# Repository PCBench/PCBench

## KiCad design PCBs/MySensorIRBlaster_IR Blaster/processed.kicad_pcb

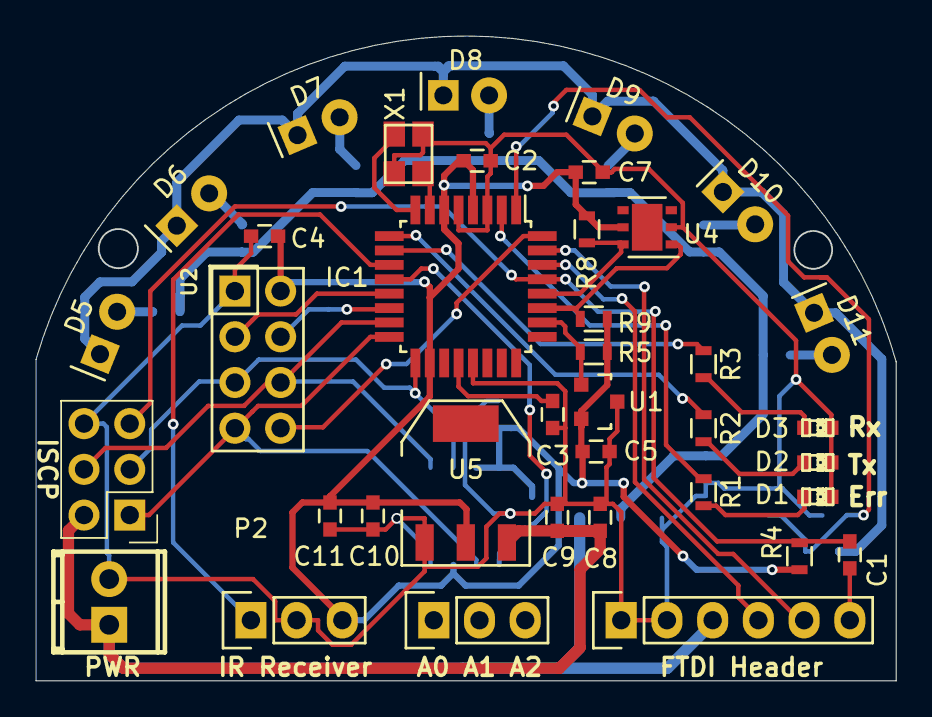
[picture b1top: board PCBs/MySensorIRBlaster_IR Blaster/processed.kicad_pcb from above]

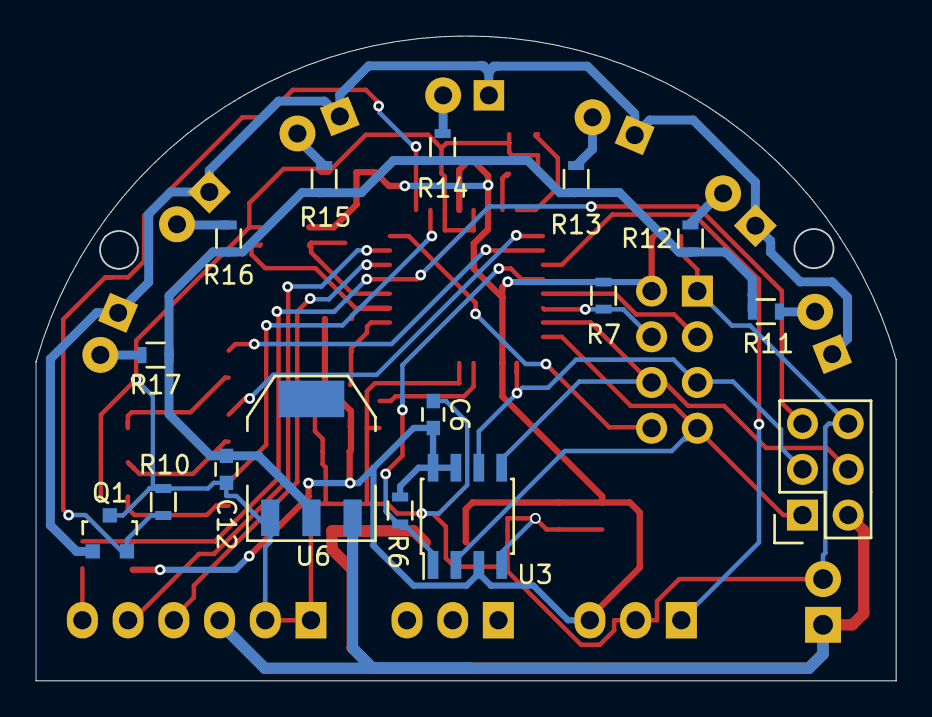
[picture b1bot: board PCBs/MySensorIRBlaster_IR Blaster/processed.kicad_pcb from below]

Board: 2 copper layers, 47.8 x 35.8 mm, 53 parts (16 on the bottom side), 37 nets.

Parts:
C1, C2, C3, C4, C5, C6, C7, C9, C11: 0.1uF; C_0603
C8, C10: 10uF; C_0603
C12: 22uF; C_0603
CON1: AVR-ISP-6; Socket_Strip_Straight_2x03
D1: Err; LED-0603
D2: Tx; LED-0603
D3: Rx; LED-0603
D5, D6, D7, D8, D9, D10, D11: IR LED; LED-5MM-Horizontal
IC1: ATMEGA328P-A; TQFP-32_7x7mm_Pitch0.8mm
P1: FTDI Header; Pin_Header_Straight_1x06
P2: IR Receiver; Socket_Strip_Straight_1x03
P3: Analog IN; Pin_Header_Straight_1x03
P4: PWR; TerminalBlock2.54mmx2-kcswalter
Q1: FDV303N; SOT-23
R1, R2, R3, R11, R12, R13, R14, R15, R16, R17: R; R_0603
R4: 10K; R_0603
R5, R6, R7, R8, R9, R10: 10k; R_0603
U1: ATSHA204A; SOT-23
U2: NRF24L01
U3: AT25DF512C; SOIC-8_3.9x4.9mm_Pitch1.27mm
U4: Si7021; DFN-6-1EP_3x3mm_Pitch0.95mm
U5: AMS1117-3.3; SOT-223
U6: AMS1117-5.0; SOT-223
X1: CRYSTAL; crystal_FA238-TSX3225

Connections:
+3V3: C2.1, C4.1, C5.1, C6.1, C7.1, C10.1, C11.1, IC1.4, IC1.6, IC1.18, P2.3, R4.1, R5.1, R6.1, R7.2, R8.2, R9.1, U1.2, U2.2, U3.3, U3.7, U3.8, U4.5, U5.2
+5V: C12.1, R11.1, R12.1, R13.1, R14.1, R15.1, R16.1, R17.1, U6.2
/A3: IC1.26, R5.2, U1.1
/D2: IC1.32, U2.8
/D3: IC1.1, Q1.2, R10.2
/D4: IC1.2, R1.2
/D5: IC1.9, R2.2
/D6: IC1.10, R3.2
/D7: IC1.11, P2.1
/D8: IC1.12, R6.2, U3.1
/D9: IC1.13, U2.3
/D10: IC1.14, R7.1, U2.4
/DTR: C1.1, P1.6
/MISO: CON1.1, IC1.16, U2.7, U3.2
/MOSI: CON1.4, IC1.15, U2.6, U3.5
/RESET: C1.2, CON1.5, IC1.29, R4.2
/RXD: IC1.30, P1.4
/SCK: CON1.3, IC1.17, U2.5, U3.6
/SCL: IC1.28, R8.1, U4.6
/SDA: IC1.27, R9.2, U4.1
/TXD: IC1.31, P1.5
/XTAL1: IC1.7, X1.1
/XTAL2: IC1.8, X1.2
GND: C2.2, C3.2, C4.2, C5.2, C6.2, C7.2, C8.2, C9.2, C10.2, C11.2, C12.2, CON1.6, D1.1, D2.1, D3.1, IC1.3, IC1.5, IC1.21, P1.1, P1.2, P2.2, P4.2, Q1.3, R10.1, U1.3, U2.1, U3.4, U4.2, U5.1, U6.1, X1.3
unnamed: C3.1, IC1.20
unnamed: D1.2, R1.1
unnamed: D2.2, R2.1
unnamed: D3.2, R3.1
unnamed: D5.2, R11.2
unnamed: D6.2, R12.2
unnamed: D7.2, R13.2
unnamed: D8.2, R14.2
unnamed: D9.2, R15.2
unnamed: D5.1, D6.1, D7.1, D8.1, D9.1, D10.1, D11.1, Q1.1
unnamed: D10.2, R16.2
unnamed: D11.2, R17.2
VCC: C8.1, C9.1, CON1.2, P1.3, P4.1, U5.3, U6.3

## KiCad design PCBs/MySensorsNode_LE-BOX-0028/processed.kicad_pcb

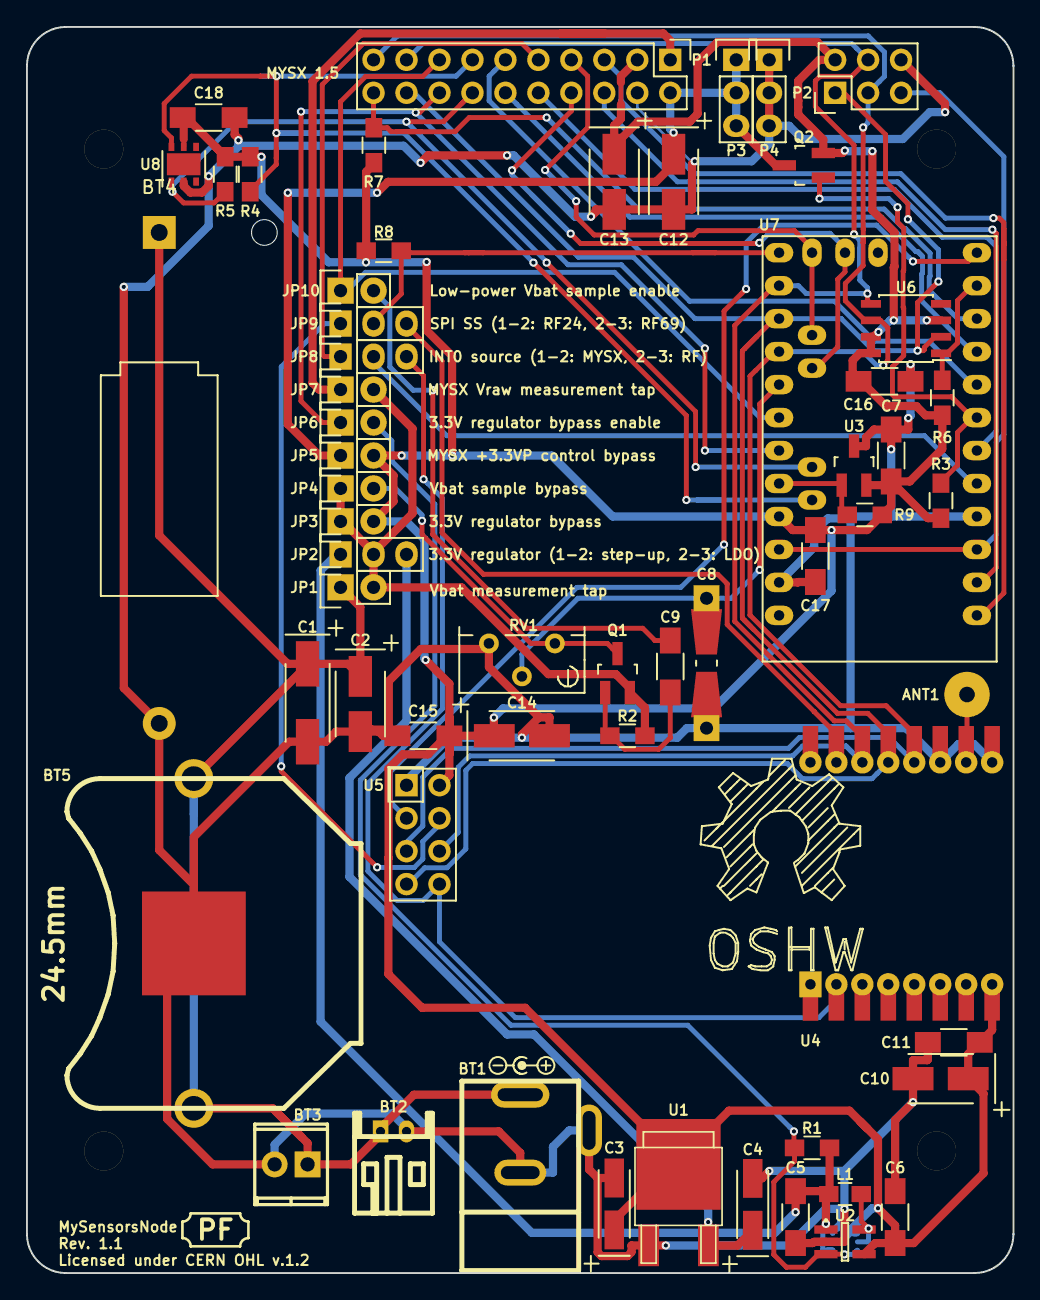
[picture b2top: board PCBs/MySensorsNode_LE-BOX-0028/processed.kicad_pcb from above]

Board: 2 copper layers, 76.0 x 96.0 mm, 66 parts (1 on the bottom side), 41 nets.

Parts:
ANT1: CONN_01X01; SolderWirePad_single_1-2mmDrill
BT1: 2.5mm jack; dc_socket-kcswalter
BT2: JST; s2b-ph-kl-kcswalter
BT3: Generic; TerminalBlock2.54mmx2-kcswalter
BT4: CR123; CR123_holder
BT5: 24.5mm; keystone_3009-kcswalter
C1: 47uF; TantalC_SizeC_EIA-6032_HandSoldering
C2, C10, C12, C13, C14: 4.7uF; TantalC_SizeB_EIA-3528_HandSoldering
C3, C4: 10uF; TantalC_SizeA_EIA-3216_HandSoldering
C5, C6: 10uF; C_1206_HandSoldering
C7, C9, C11, C15, C16, C17, C18: 0.1uF; C_1206_HandSoldering
C8: C; Resistor_SMD+THTuniversal_0805to1206_RM10_HandSoldering
HOLE1, HOLE2, HOLE3, HOLE4: MountingHole_2.5mm; MountingHole_3mm
JP1, JP3, JP4, JP5, JP6, JP7, JP10: Jumper_NO_Small; Pin_Header_Straight_1x02
JP2, JP8, JP9: JUMPER3; Pin_Header_Straight_1x03
L1: 4.7uH; C_0805_HandSoldering
OPHW_LOGO: Symbol_OSHW-Logo_SilkScreen_BIG
P1: MYSX_1.5
P2: CONN_02X03; Pin_Header_Straight_2x03
P3, P4: CONN_01X03; Pin_Header_Straight_1x03
PLUG_SPEC: LOGO; Logo_silk_polarity_center_5x1.4mm
Q1, Q2: DMP3056L-7; SOT-23_Handsoldering
R1: 150K; R_0805_HandSoldering
R2, R3, R4, R5: 10K; R_0805_HandSoldering
R6, R7, R8, R9: 56K; R_0805_HandSoldering
RV1: 1M; Potentiometer_Bourns_3296Y_3-8Zoll_Angular_ScrewUp
U1: LD1117DT33TR; d-pak-kcswalter
U2: TPS61097A; SOT-23-5_Handsoldering
U3: ATSHA204A; SOT-23_Handsoldering
U4: RFM69HW; RFM69HW_SMD_ThroughHole_Handsoldering
U5: NRF24L01
U6: AT25DF512C; SOIC-8_3.9x4.9mm_Pitch1.27mm
U7: ArduinoProMini; pro_mini
U8: Si7021; DFN-6-1EP_3x3mm_Pitch0.95mm
U9: TPS61221; SC-70-6

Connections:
+3.3VP: C12.1, JP5.1, P1.2, P3.1, P3.2, P3.3, Q2.3
+3V3: C3.1, C6.1, C7.1, C10.1, C11.2, C13.1, C14.1, C15.2, C16.2, C17.1, C18.1, JP3.2, JP5.2, P1.3, P2.2, Q2.2, R3.2, R4.2, R5.2, R6.2, R7.2, R8.1, R9.2, U1.2, U2.4, U3.2, U4.8, U5.2, U6.3, U6.7, U6.8, U7.21, U8.5, U9.2, U9.4
+BATT: JP1.2, JP2.2, JP3.1, JP4.1, JP7.2, Q1.2, R2.2
/MISO: P1.18, P2.1, U4.13, U5.7, U6.2, U7.15
/MOSI: P1.17, P2.4, U4.14, U5.6, U6.5, U7.14
/SCK: P1.19, P2.3, U4.12, U5.5, U6.6, U7.16
ATSHA_SDA: R9.1, U3.1, U7.20
FLASH_CSN: R6.1, U6.1, U7.11
GND: BT1.1, BT1.2, BT2.2, BT3.2, BT4.2, BT5.2, C1.2, C2.2, C3.2, C4.2, C5.2, C6.2, C7.2, C8.2, C10.2, C11.1, C12.2, C13.2, C14.2, C15.1, C16.1, C17.2, C18.2, P1.4, P2.6, P4.1, P4.2, P4.3, RV1.3, U1.1, U2.2, U3.3, U4.9, U4.11, U5.1, U7.4, U7.23, U8.2, U9.3
MYSX_3.3V_EN: Q2.1, R3.1, U7.7
MYSX_A1: P1.7, U7.27
MYSX_A2: P1.8, U7.28
MYSX_D1_DFM: P1.5, U7.1
MYSX_D2_DTM: P1.6, U7.2
MYSX_D3_INT: JP8.1, P1.9
MYSX_D4_INT: P1.10, U7.6
MYSX_D5_PWM: P1.11, U7.8
MYSX_D6_PWM: P1.12, U7.9
MYSX_D7_SCL: P1.13, R4.1, U7.26, U8.6
MYSX_D8_SDA: P1.14, R5.1, U7.25, U8.1
MYSX_D9_A3: JP10.1, P1.15, U7.18
MYSX_D10_A4: JP6.1, P1.16, U7.19
MYSX_D14_CS: P1.20, R7.1, U7.10
unnamed: ANT1.1, U4.10
unnamed: BT1.3, BT2.1, BT3.1, BT4.1, BT5.1, C1.1, C2.1, JP1.1
unnamed: C4.1, JP2.3, U1.3
unnamed: C5.1, JP2.1, L1.2, R1.1, U2.1, U9.1
unnamed: C9.1, JP10.2
unnamed: C9.2, Q1.1, R2.1
unnamed: JP4.2, Q1.3, RV1.1
unnamed: JP6.2, R1.2, U2.3, U9.6
unnamed: JP7.1, P1.1
unnamed: JP8.2, U7.5
unnamed: JP9.2, R8.2, U7.13
unnamed: L1.1, U2.5, U9.5
RESET: P2.5, U7.3, U7.22
RF24_CE: U5.3, U7.12
RF24_CSN: JP9.1, U5.4
RF69_NSS: JP9.3, U4.15
RF_INT: JP8.3, U4.2, U5.8
VBAT_SMPL: C8.1, RV1.2, U7.17

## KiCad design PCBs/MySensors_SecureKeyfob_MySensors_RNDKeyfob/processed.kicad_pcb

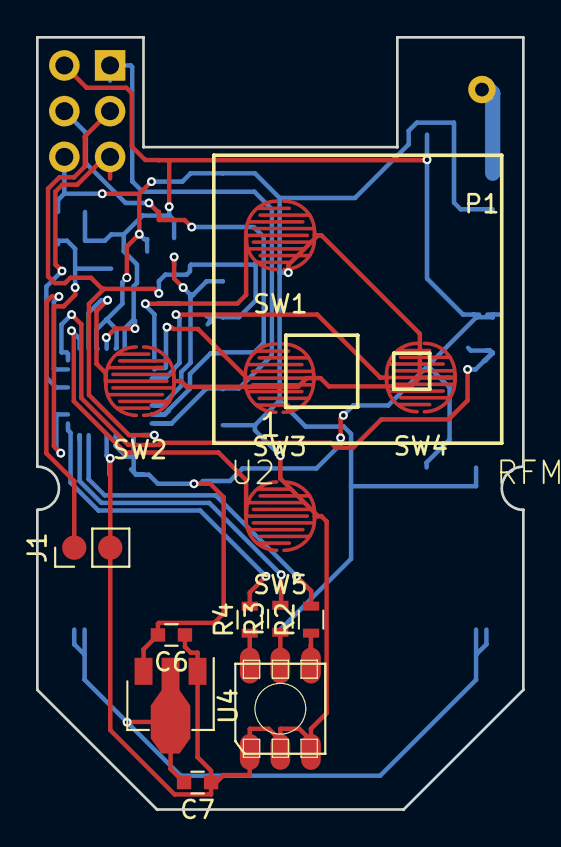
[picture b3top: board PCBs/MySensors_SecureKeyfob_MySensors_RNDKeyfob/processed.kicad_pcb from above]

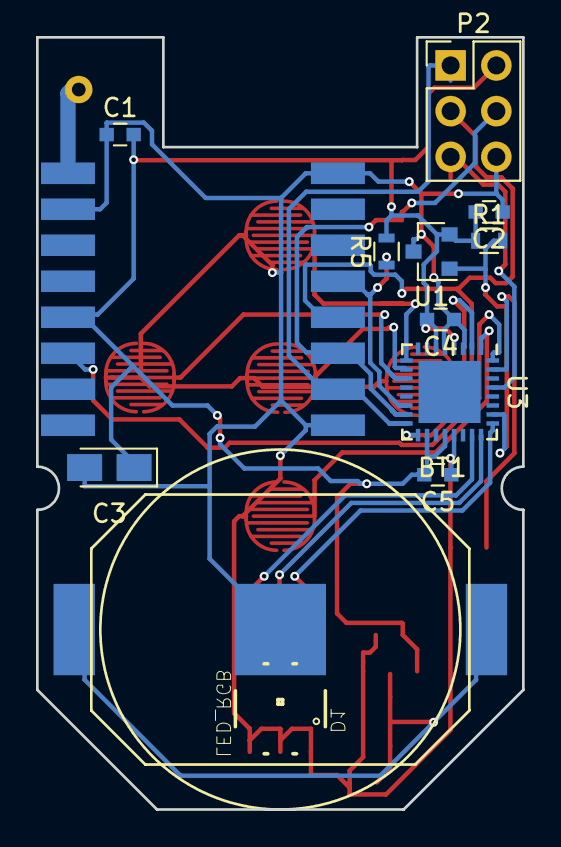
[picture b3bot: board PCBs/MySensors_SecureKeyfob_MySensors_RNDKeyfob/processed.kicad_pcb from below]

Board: 2 copper layers, 27.0 x 42.9 mm, 26 parts (12 on the bottom side), 23 nets.

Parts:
BT1: Battery; CR2032Holder
C1, C2, C4, C5: 100n; C_0603
C3: CP; CP_Tantalum_Case-A_EIA-3216-18_Reflow
C6, C7: C; C_0603
D1: LED_RGB; LED-TRICOLOR-5050
J1: CONN_01X02; Pin_Header_Straight_1x02_Pitch2.00mm
P1: CONN_01X01; 868MHz_Spring_Antenna
P2: CONN_02X03; Pin_Header_Straight_2x03_Pitch2.54mm
R1: 1K; R_0603
R2, R3, R4, R5: R; R_0603
SW1, SW2, SW3, SW4, SW5: SW_SPST; 4mm_Rubber_Button
U1: ATSHA204A; SOT-23
U2: RFM69HCW; RFM69HCW-XXXS2
U3: ATMEGA328P-MU; QFN-32-1EP_5x5mm_Pitch0.5mm
U4: HT7333; SOT-89-3

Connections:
/A0: R2.2, U3.23
/A1: R3.2, U3.24
/A2: R4.2, U3.25
/A3: R1.2, U1.1, U3.26
/ANT: P1.1, U2.9
/D2: U2.14, U3.32
/D3: SW5.1, U3.1
/D4: SW2.1, U3.2
/D5: SW1.1, U3.9
/D6: SW3.1, U3.10
/D7: SW4.1, U3.11
/D10: R5.1, U2.5, U3.14
/MISO: P2.1, U2.2, U3.16
/MOSI: P2.4, U2.3, U3.15
/RESET: P2.5, U3.29
/SCK: P2.3, U2.4, U3.17
/TXO: J1.1, U3.31
/VCC: C1.2, C2.2, C3.1, C4.2, C5.2, C6.2, P2.2, R1.1, R5.2, U1.2, U2.13, U3.4, U3.6, U3.18, U3.20, U4.3
GND: BT1.2, C1.1, C2.1, C3.2, C4.1, C5.1, C6.1, C7.1, D1.1, D1.2, D1.3, J1.2, P2.6, SW1.2, SW2.2, SW3.2, SW4.2, SW5.2, U1.3, U2.1, U2.8, U2.10, U3.3, U3.5, U3.21, U4.1
unnamed: BT1.1, C7.2, U4.2
unnamed: D1.4, R2.1
unnamed: D1.5, R3.1
unnamed: D1.6, R4.1

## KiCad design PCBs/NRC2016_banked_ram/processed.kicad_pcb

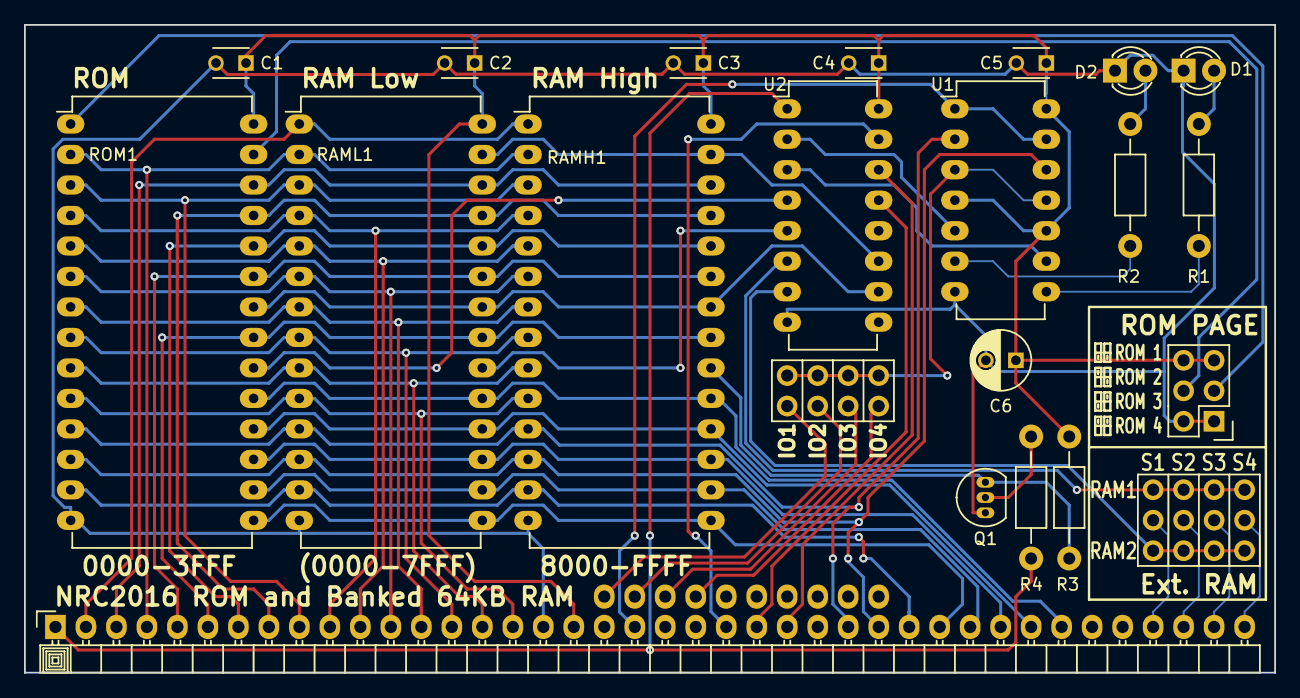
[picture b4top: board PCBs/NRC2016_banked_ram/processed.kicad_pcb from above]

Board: 2 copper layers, 104.1 x 54.0 mm, 24 parts (0 on the bottom side), 55 nets.

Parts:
C1, C2, C3, C4, C5: C; C_Disc_D3_P2.5
C6: CP; C_Radial_D5_L11_P2.5
D1, D2: LED; LED-3MM
LOGO1: BackLogo; nrc2016_top_logo_1600
P1: IO_BUS_PINS; Pin_Header_Angled_1x10_nrc2016
P2: CONN_02X04; Pin_Header_Straight_2x04_nrc2016
P3: CONN_02X03; Pin_Header_Straight_2x03
P4: Z80_BUS_PINS; Pin_Header_Angled_1x40_nrc2016
Q1: Q_NPN_EBC; TO-92_Inline_Narrow_Oval
R1, R2, R3, R4: R; Resistor_Horizontal_RM10mm
RAMH1: 62256; DIP-28_W15.24mm_LongPads
RAML1: 62256; DIP-28_W15.24mm_LongPads
RAMSEL1: CONN_04x03; ramsel_pins
ROM1: 27C512; DIP-28_W15.24mm_LongPads
U1: 74LS74; DIP-14_W7.62mm_LongPads
U2: 74LS139; DIP-16_W7.62mm_LongPads

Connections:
/A0: P4.16, RAMH1.10, RAML1.10, ROM1.10
/A1: P4.15, RAMH1.9, RAML1.9, ROM1.9
/A2: P4.14, RAMH1.8, RAML1.8, ROM1.8
/A3: P4.13, RAMH1.7, RAML1.7, ROM1.7
/A4: P4.12, RAMH1.6, RAML1.6, ROM1.6
/A5: P4.11, RAMH1.5, RAML1.5, ROM1.5
/A6: P4.10, RAMH1.4, RAML1.4, ROM1.4
/A7: P4.9, RAMH1.3, RAML1.3, ROM1.3
/A8: P4.8, RAMH1.25, RAML1.25, ROM1.25
/A9: P4.7, RAMH1.24, RAML1.24, ROM1.24
/A10: P4.6, RAMH1.21, RAML1.21, ROM1.21
/A11: P4.5, RAMH1.23, RAML1.23, ROM1.23
/A12: P4.4, RAMH1.2, RAML1.2, ROM1.2
/A13: P4.3, RAMH1.26, RAML1.26, ROM1.26
/A14: P4.2, RAMH1.1, RAML1.1
/A15: P4.1, R4.1, U2.1
/D0: P4.27, RAMH1.11, RAML1.11, ROM1.11, U1.2
/D1: P4.28, RAMH1.12, RAML1.12, ROM1.12, U1.12
/D2: P4.29, RAMH1.13, RAML1.13, ROM1.13
/D3: P4.30, RAMH1.15, RAML1.15, ROM1.15
/D4: P4.31, RAMH1.16, RAML1.16, ROM1.16
/D5: P4.32, RAMH1.17, RAML1.17, ROM1.17
/D6: P4.33, RAMH1.18, RAML1.18, ROM1.18
/D7: P4.34, RAMH1.19, RAML1.19, ROM1.19
/~EXT_RAM1: RAMSEL1.1, RAMSEL1.2, RAMSEL1.3, RAMSEL1.4, U2.6
/~EXT_RAM2: RAMSEL1.9, RAMSEL1.10, RAMSEL1.11, RAMSEL1.12, U2.7
/~MREQ: P4.23, U2.15
/~RAMH_CS: Q1.3, R3.2, RAMH1.20
/~RAML_CS: RAML1.20, U2.5
/~RD: P4.25, U2.14
/~READ: RAMH1.22, RAML1.22, ROM1.22, U2.10
/~RESET: P4.20, U1.1, U1.13
/~ROM_CS: ROM1.20, U2.4
/~WR: P4.24, U2.13
/~WRITE: RAMH1.27, RAML1.27, U2.11
GND: C1.2, C2.2, C3.2, C4.2, C5.2, C6.2, D1.1, D2.1, P3.1, P3.2, P4.17, Q1.1, RAMH1.14, RAML1.14, ROM1.14, U1.7, U2.8
unnamed: D1.2, R1.2
unnamed: D2.2, R2.2
unnamed: P1.1, P2.1
unnamed: P1.2, P2.3
unnamed: P1.3, P2.5
unnamed: P1.4, P2.7
unnamed: P2.2, P2.4, P2.6, P2.8, U1.3, U1.11
unnamed: P3.3, ROM1.1
unnamed: P3.4, ROM1.27
unnamed: P4.37, RAMSEL1.8
unnamed: P4.38, RAMSEL1.7
unnamed: P4.39, RAMSEL1.6
unnamed: P4.40, RAMSEL1.5
unnamed: Q1.2, R4.2
unnamed: R1.1, U1.8
unnamed: R2.1, U1.6
unnamed: U1.5, U2.2
unnamed: U1.9, U2.3
VCC: C1.1, C2.1, C3.1, C4.1, C5.1, C6.1, P3.5, P3.6, P4.18, R3.1, RAMH1.28, RAML1.28, ROM1.28, U1.4, U1.10, U1.14, U2.16

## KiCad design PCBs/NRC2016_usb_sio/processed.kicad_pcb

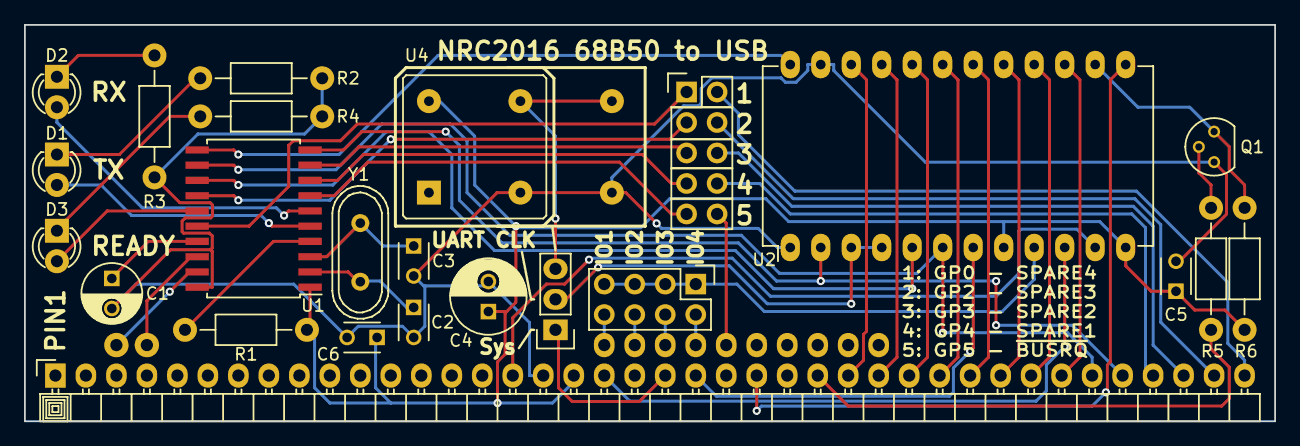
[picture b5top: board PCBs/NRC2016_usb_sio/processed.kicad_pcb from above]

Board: 2 copper layers, 104.1 x 33.0 mm, 27 parts (0 on the bottom side), 51 nets.

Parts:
C1: 1uF; C_Radial_D5_L6_P2.5
C2, C3: 22pF; C_Disc_D3_P2.5
C4: 10uF; C_Radial_D6.3_L11.2_P2.5
C5, C6: 100nF; C_Disc_D3_P2.5
CON1: USB; Pin_Header_Angled_1x02_nrc2016
D1: TX LED; LED-3MM
D2: RX LED; LED-3MM
D3: USB RDY; LED-3MM
JP1: JUMPER3; Pin_Header_Straight_1x03
LOGO1: BackLogo; nrc2016_top_logo_1600
P1: Z80_BUS_PINS; Pin_Header_Angled_1x40_nrc2016
P2: IO_BUS_PINS; Pin_Header_Angled_1x10_nrc2016
P3: CONN_02X05; Pin_Header_Straight_2x05
P4: CONN_02X04; Pin_Header_Straight_2x04
Q1: Q_NPN_EBC; TO-92_Molded_Narrow
R1, R5: 10K; Resistor_Horizontal_RM10mm
R2, R3, R4: 220; Resistor_Horizontal_RM10mm
R6: 2K2; Resistor_Horizontal_RM10mm
U1: MCP2200; SOIC-20W_7.5x12.8mm_Pitch1.27mm
U2: 68B50; DIP-24_W15.24mm_LongPads
U4: 1.8432MHz; OSC_MULTIPACKAGE_DIP
Y1: 12MHz; Crystal_HC49-U_Vertical

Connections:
/A0: P1.16, U2.11
/D0: P1.27, U2.22
/D1: P1.28, U2.21
/D2: P1.29, U2.20
/D3: P1.30, U2.19
/D4: P1.31, U2.18
/D5: P1.32, U2.17
/D6: P1.33, U2.16
/D7: P1.34, U2.15
/ENA: Q1.3, R6.2, U2.14
/GP0: P3.1, U1.16
/GP2: P3.3, U1.14
/GP3: P3.5, U1.9
/GP4: P3.7, U1.8
/GP5: P3.9, U1.7
/RX: P1.36, U1.10, U2.2
/S1: P1.37, P3.8
/S2: P1.38, P3.6
/S3: P1.39, P3.4
/S4: P1.40, P3.2
/TX: P1.35, U1.12, U2.6
/~BUSRQ: P2.5, P3.10
/~CLK: JP1.1, P1.21
/~INT: P1.22, U2.7
/~IORQ: P1.26, R5.2
/~IOSEL: P4.1, P4.3, P4.5, P4.7, U2.9
/~M1: P1.19, U2.10
/~WR: P1.24, U2.13
GND: C1.2, C2.2, C3.2, C4.2, C5.2, C6.2, P1.17, Q1.1, R2.1, R3.1, R4.1, U1.20, U2.1, U2.23, U4.GND
unnamed: C1.1, U1.17
unnamed: C2.1, U1.2, Y1.1
unnamed: C3.1, U1.3, Y1.2
unnamed: CON1.1, U1.19
unnamed: CON1.2, U1.18
unnamed: D1.1, R2.2
unnamed: D1.2, U1.5
unnamed: D2.1, R3.2
unnamed: D2.2, U1.6
unnamed: D3.1, R4.2
unnamed: D3.2, U1.15
unnamed: JP1.2, U2.3, U2.4
unnamed: JP1.3, U4.OUT
unnamed: P2.1, P4.8
unnamed: P2.2, P4.6
unnamed: P2.3, P4.4
unnamed: P2.4, P4.2
unnamed: Q1.2, R5.1
unnamed: R1.2, U1.4
unnamed: U1.11, U2.24
unnamed: U1.13, U2.5
VCC: C4.1, C5.1, C6.1, P1.18, R1.1, R6.1, U1.1, U2.8, U2.12, U4.VCC

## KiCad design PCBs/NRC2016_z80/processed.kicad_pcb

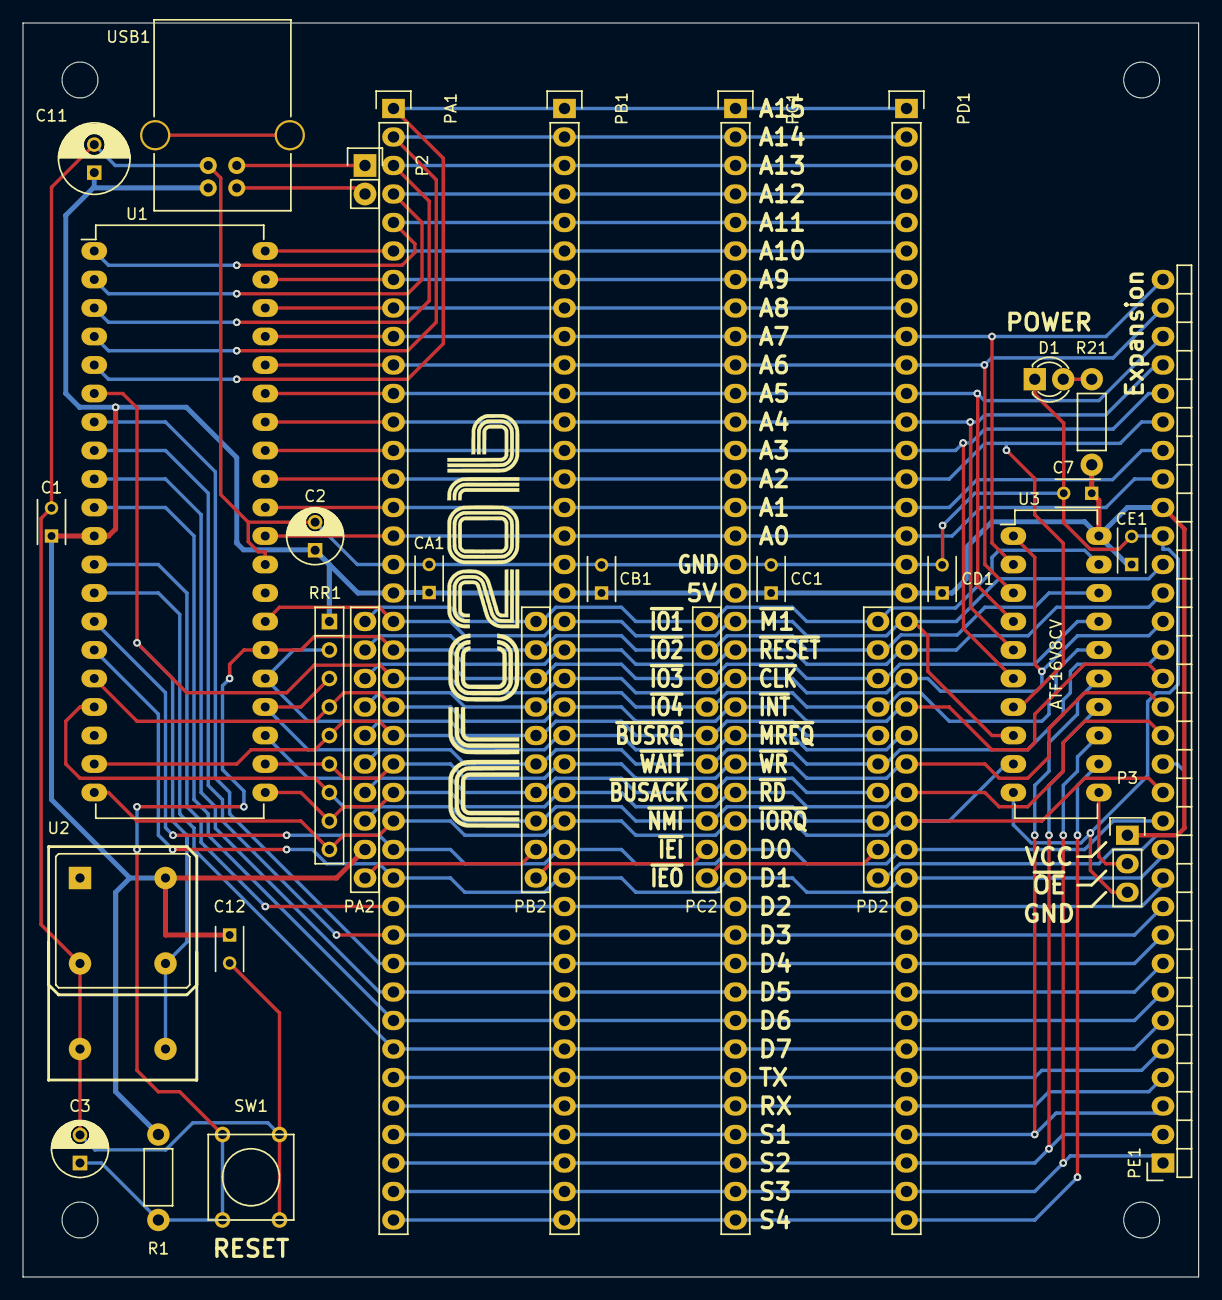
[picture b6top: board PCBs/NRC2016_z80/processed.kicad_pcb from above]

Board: 2 copper layers, 104.8 x 111.8 mm, 37 parts (0 on the bottom side), 56 nets.

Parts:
C1, C7, C12: 100n; C_Rect_L4_W2.5_P2.5
C2, C3: 1uF; C_Radial_D5_L6_P2.5
C11: 10u; C_Radial_D6.3_L11.2_P2.5
CA1: 100n; C_Rect_L4_W2.5_P2.5
CB1: 100n; C_Rect_L4_W2.5_P2.5
CC1: 100n; C_Rect_L4_W2.5_P2.5
CD1: 100n; C_Rect_L4_W2.5_P2.5
CE1: 100n; C_Rect_L4_W2.5_P2.5
D1: LED; LED-3MM
LOGO1: FrontLogo; nrc2016_top_logo_1600
LOGO2: BackLogo; nrc2016_bottom_logo_600_v2
MH1, MH2, MH3, MH4: MH_3mm; MountingHole_3.2mm_M3
P2: USB_SOCKET; Socket_Strip_Straight_1x02
P3: Jumper; Pin_Header_Straight_1x03
PA1: Z80_BUS_SOCKET; Socket_Strip_Straight_1x40
PA2: IO_BUS_SOCKET; Socket_Strip_Straight_1x10_NRC2016
PB1: Z80_BUS_SOCKET; Socket_Strip_Straight_1x40
PB2: IO_BUS_SOCKET; Socket_Strip_Straight_1x10_NRC2016
PC1: Z80_BUS_SOCKET; Socket_Strip_Straight_1x40
PC2: IO_BUS_SOCKET; Socket_Strip_Straight_1x10_NRC2016
PD1: Z80_BUS_SOCKET; Socket_Strip_Straight_1x40
PD2: IO_BUS_SOCKET; Socket_Strip_Straight_1x10_NRC2016
PE1: EXPANSION_SOCKET; Socket_Strip_Angled_1x32_nrc2016
R1: 10K; Resistor_Horizontal_RM7mm
R21: 220; Resistor_Horizontal_RM7mm
RR1: RR8; Resistor_Array_SIP8
SW1: RESET; SW_PUSH_SMALL
U1: Z80CPU; DIP-40_W15.24mm_LongPads
U2: DIP_OSCILLATOR; OSC_MULTIPACKAGE_DIP
U3: ATF16V8CV; DIP-20_W7.62mm_LongPads
USB1: USB_B

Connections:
/A0: PA1.16, PB1.16, PC1.16, PD1.16, PE1.25, U1.30
/A1: PA1.15, PB1.15, PC1.15, PD1.15, PE1.26, U1.31
/A2: PA1.14, PB1.14, PC1.14, PD1.14, PE1.27, U1.32, U3.7
/A3: PA1.13, PB1.13, PC1.13, PD1.13, PE1.28, U1.33, U3.6
/A4: PA1.12, PB1.12, PC1.12, PD1.12, PE1.29, U1.34, U3.5
/A5: PA1.11, PB1.11, PC1.11, PD1.11, PE1.30, U1.35, U3.4
/A6: PA1.10, PB1.10, PC1.10, PD1.10, PE1.31, U1.36, U3.3
/A7: PA1.9, PB1.9, PC1.9, PD1.9, PE1.32, U1.37, U3.2
/A8: PA1.8, PB1.8, PC1.8, PD1.8, U1.38
/A9: PA1.7, PB1.7, PC1.7, PD1.7, U1.39
/A10: PA1.6, PB1.6, PC1.6, PD1.6, U1.40
/A11: PA1.5, PB1.5, PC1.5, PD1.5, U1.1
/A12: PA1.4, PB1.4, PC1.4, PD1.4, U1.2
/A13: PA1.3, PB1.3, PC1.3, PD1.3, U1.3
/A14: PA1.2, PB1.2, PC1.2, PD1.2, U1.4
/A15: PA1.1, PB1.1, PC1.1, PD1.1, U1.5
/Card Slots/Expansion/IEI: PD2.10, PE1.15
/Card Slots/PortB/IEI: PA2.10, PB2.9
/Card Slots/PortC/IEI: PB2.10, PC2.9
/Card Slots/PortD/IEI: PC2.10, PD2.9
/Card Slots/RX: PA1.36, PB1.36, PC1.36, PD1.36, PE1.4
/Card Slots/S1: PA1.37, PB1.37, PC1.37, PD1.37, PE1.3, U3.15
/Card Slots/S2: PA1.38, PB1.38, PC1.38, PD1.38, PE1.2, U3.14
/Card Slots/S3: PA1.39, PB1.39, PC1.39, PD1.39, PE1.1, U3.13
/Card Slots/S4: PA1.40, PB1.40, PC1.40, PD1.40, U3.12
/Card Slots/TX: PA1.35, PB1.35, PC1.35, PD1.35, PE1.5
/Card Slots/~IOSEL0: PA2.1, PB2.1, PC2.1, PD2.1, U3.19
/Card Slots/~IOSEL1: PA2.2, PB2.2, PC2.2, PD2.2, U3.18
/Card Slots/~IOSEL2: PA2.3, PB2.3, PC2.3, PD2.3, U3.17
/Card Slots/~IOSEL3: PA2.4, PB2.4, PC2.4, PD2.4, U3.16
/D0: PA1.27, PB1.27, PC1.27, PD1.27, PE1.13, U1.14
/D1: PA1.28, PB1.28, PC1.28, PD1.28, PE1.12, U1.15
/D2: PA1.29, PB1.29, PC1.29, PD1.29, PE1.11, U1.12
/D3: PA1.30, PB1.30, PC1.30, PD1.30, PE1.10, U1.8
/D4: PA1.31, PB1.31, PC1.31, PD1.31, PE1.9, U1.7
/D5: PA1.32, PB1.32, PC1.32, PD1.32, PE1.8, U1.9
/D6: PA1.33, PB1.33, PC1.33, PD1.33, PE1.7, U1.10
/D7: PA1.34, PB1.34, PC1.34, PD1.34, PE1.6, U1.13
/~BUSACK: PA2.7, PB2.7, PC2.7, PD2.7, U1.23
/~BUSRQ: PA2.5, PB2.5, PC2.5, PD2.5, RR1.2, U1.25
/~CLK: PA1.21, PB1.21, PC1.21, PD1.21, PE1.20, U1.6, U2.OUT, U3.1
/~INT: PA1.22, PB1.22, PC1.22, PD1.22, PE1.18, RR1.4, U1.16
/~IORQ: PA1.26, PB1.26, PC1.26, PD1.26, PE1.14, RR1.9, U1.20, U3.9
/~M1: PA1.19, PB1.19, PC1.19, PD1.19, PE1.22, U1.27, U3.8
/~MREQ: PA1.23, PB1.23, PC1.23, PD1.23, RR1.5, U1.19
/~NMI: PA2.8, PB2.8, PC2.8, PD2.8, RR1.7, U1.17
/~RD: PA1.25, PB1.25, PC1.25, PD1.25, PE1.16, RR1.8, U1.21
/~RESET: C3.1, PA1.20, PB1.20, PC1.20, PD1.20, PE1.21, R1.1, SW1.2, U1.26
/~WAIT: PA2.6, PB2.6, PC2.6, PD2.6, PE1.19, RR1.3, U1.24
/~WR: PA1.24, PB1.24, PC1.24, PD1.24, PE1.17, RR1.6, U1.22
GND: C1.2, C2.2, C3.2, C7.2, C11.2, C12.2, CA1.2, CB1.2, CC1.2, CD1.2, CE1.2, D1.1, P3.3, PA1.17, PB1.17, PC1.17, PD1.17, PE1.23, SW1.1, U1.29, U2.GND, U3.10, USB1.4
unnamed: D1.2, R21.2
unnamed: P2.1, USB1.3
unnamed: P2.2, USB1.2
unnamed: P3.2, U3.11
VCC: C1.1, C2.1, C7.1, C11.1, C12.1, CA1.1, CB1.1, CC1.1, CD1.1, CE1.1, P3.1, PA1.18, PA2.9, PB1.18, PC1.18, PD1.18, PE1.24, R1.2, R21.1, RR1.1, U1.11, U2.VCC, U3.20, USB1.1

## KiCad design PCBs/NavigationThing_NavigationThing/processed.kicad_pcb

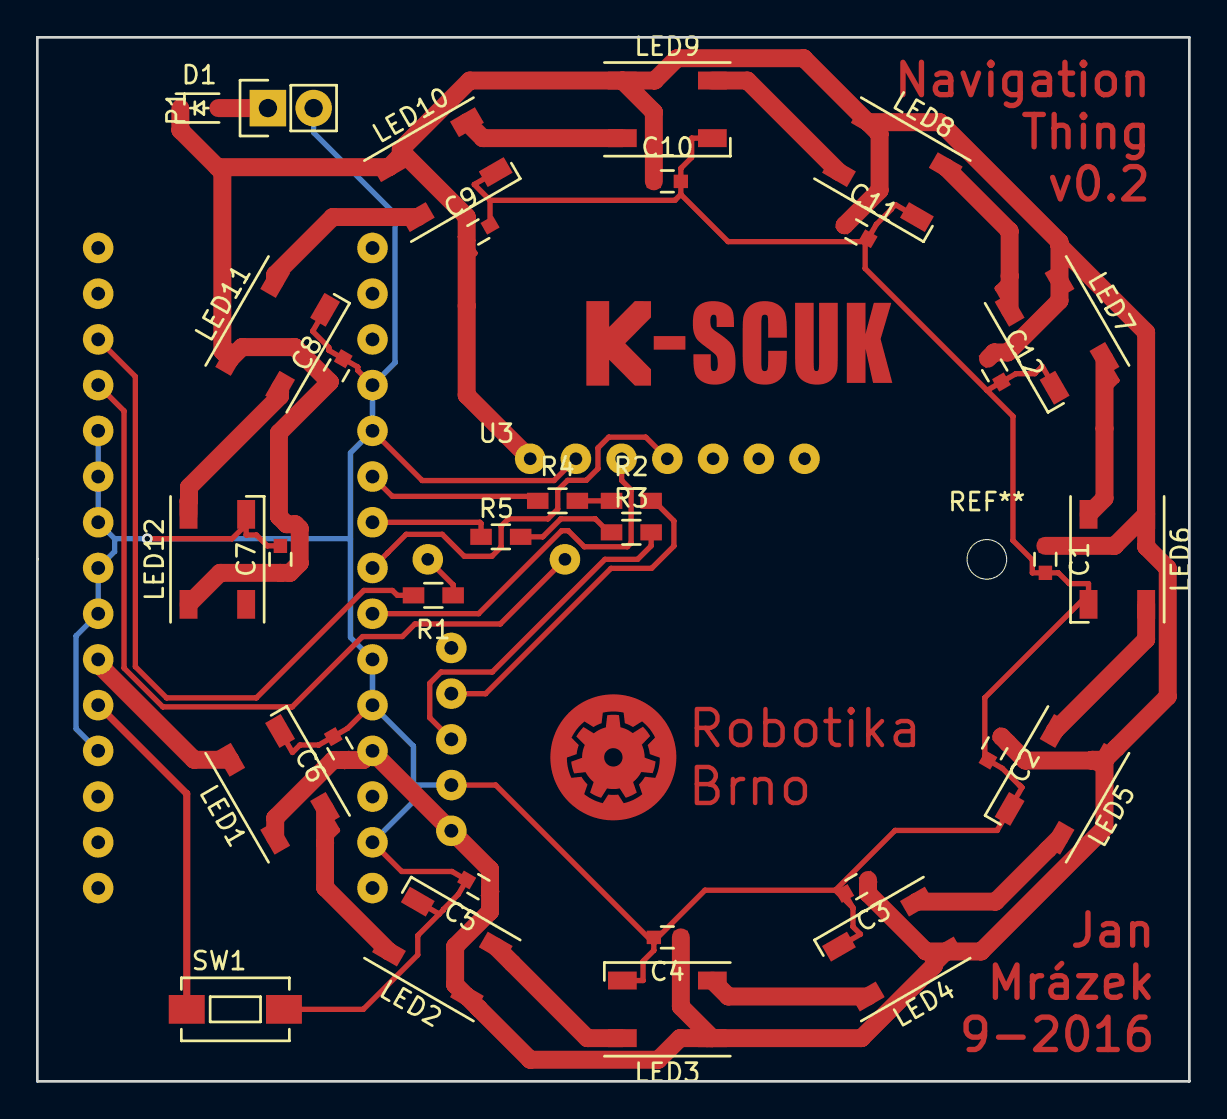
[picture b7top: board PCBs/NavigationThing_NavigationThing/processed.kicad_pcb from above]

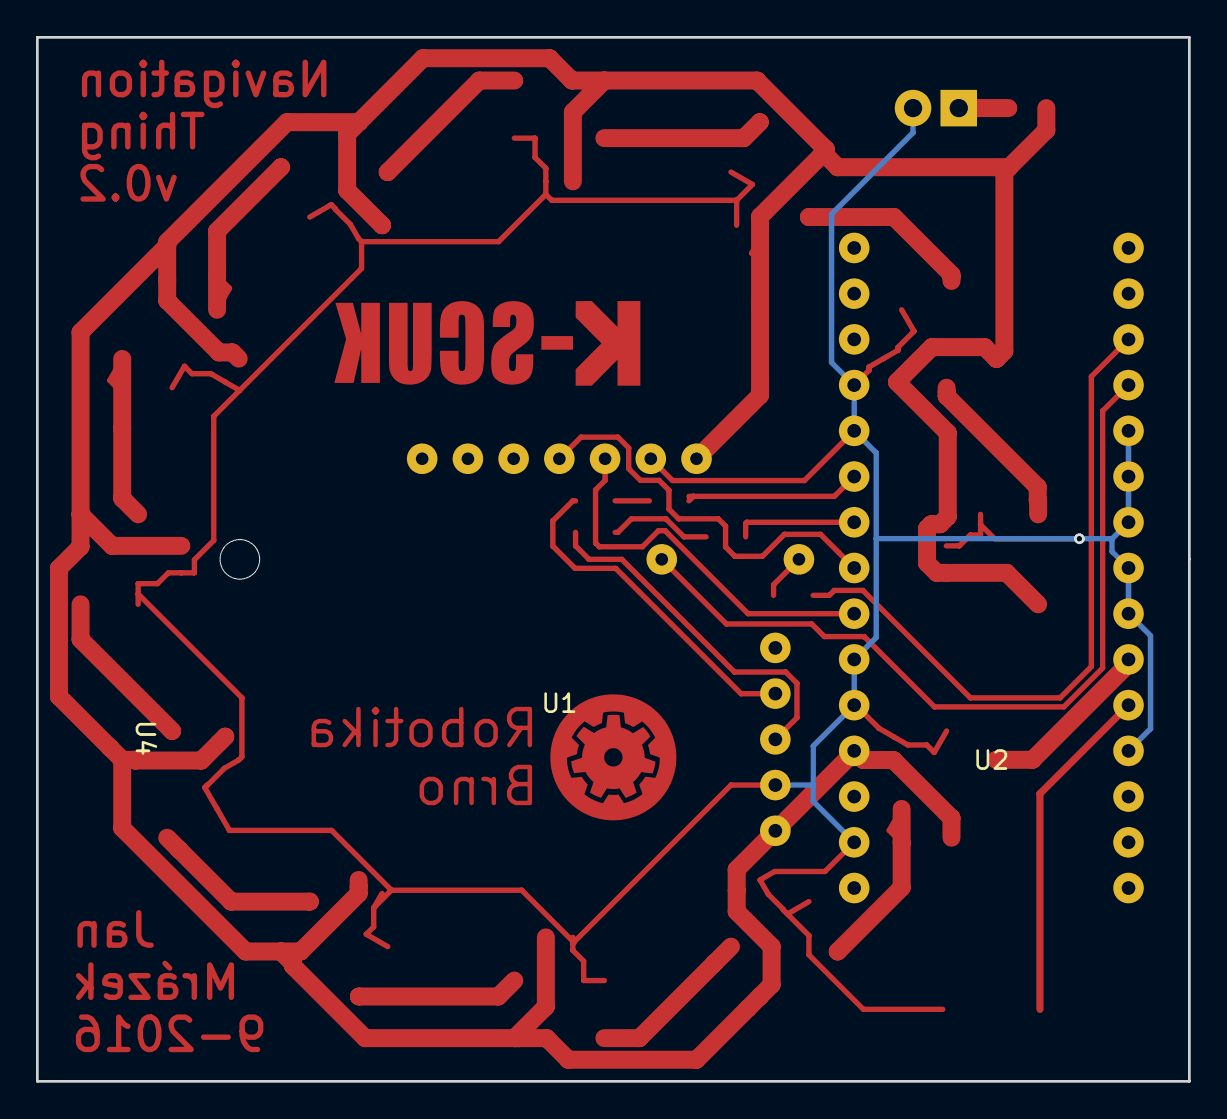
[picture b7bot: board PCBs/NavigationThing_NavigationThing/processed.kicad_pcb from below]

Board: 2 copper layers, 64.0 x 58.0 mm, 38 parts (3 on the bottom side), 27 nets.

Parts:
C1, C2, C3, C4, C5, C6, C7, C8, C9, C10, C11, C12: 100n; C_0603
D1: D; SOD-323
LED1, LED2, LED3, LED4, LED5, LED6, LED7, LED8, LED9, LED10, LED11, LED12: WS2812B; LED_WS2812B-PLCC4
P1: CONN_01X02; Pin_Header_Straight_1x02
R1: 100R; R_0603_HandSoldering
R2, R3, R4, R5: 0R; R_0603_HandSoldering
SW1: SW_PUSH; SW_SPST_EVQPE1
U1: HMC5983_module
U2: arduino_nano
U3: PIEZO; piezo_12
U4: NEO-6M_module
svg2mod: G***; kscuk_cu_17mm
svg2mod_2: G***; robotarna_cu_7mm

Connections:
+5V: C1.1, C2.1, C3.1, C4.1, C5.1, C6.1, C7.1, C8.1, C9.1, C10.1, C11.1, C12.1, D1.1, LED1.1, LED2.1, LED3.1, LED4.1, LED5.1, LED6.1, LED7.1, LED8.1, LED9.1, LED10.1, LED11.1, LED12.1, U1.1, U2.12, U4.5
GND: C1.2, C2.2, C3.2, C4.2, C5.2, C6.2, C7.2, C8.2, C9.2, C10.2, C11.2, C12.2, LED1.3, LED2.3, LED3.3, LED4.3, LED5.3, LED6.3, LED7.3, LED8.3, LED9.3, LED10.3, LED11.3, LED12.3, P1.2, SW1.2, U1.2, U2.4, U2.5, U2.10, U2.11, U2.14, U2.19, U2.22, U2.23, U2.24, U2.25, U2.26, U4.4
LED_DATA: LED1.4, U2.21
unnamed: D1.2, P1.1
unnamed: LED1.2, LED2.4
unnamed: LED2.2, LED3.4
unnamed: LED3.2, LED4.4
unnamed: LED4.2, LED5.4
unnamed: LED5.2, LED6.4
unnamed: LED6.2, LED7.4
unnamed: LED7.2, LED8.4
unnamed: LED8.2, LED9.4
unnamed: LED10.2, LED11.4
unnamed: LED9.2, LED10.4
unnamed: LED11.2, LED12.4
unnamed: R1.1, U3.2
unnamed: R1.2, U2.28
unnamed: R2.1, R4.2
unnamed: R2.2, U4.2
unnamed: R3.1, R5.2
unnamed: R3.2, U4.3
unnamed: R4.1, U2.6
unnamed: R5.1, U2.7
unnamed: SW1.1, U2.20
unnamed: U1.3, U2.9
unnamed: U1.4, U2.8
unnamed: U2.27, U3.1

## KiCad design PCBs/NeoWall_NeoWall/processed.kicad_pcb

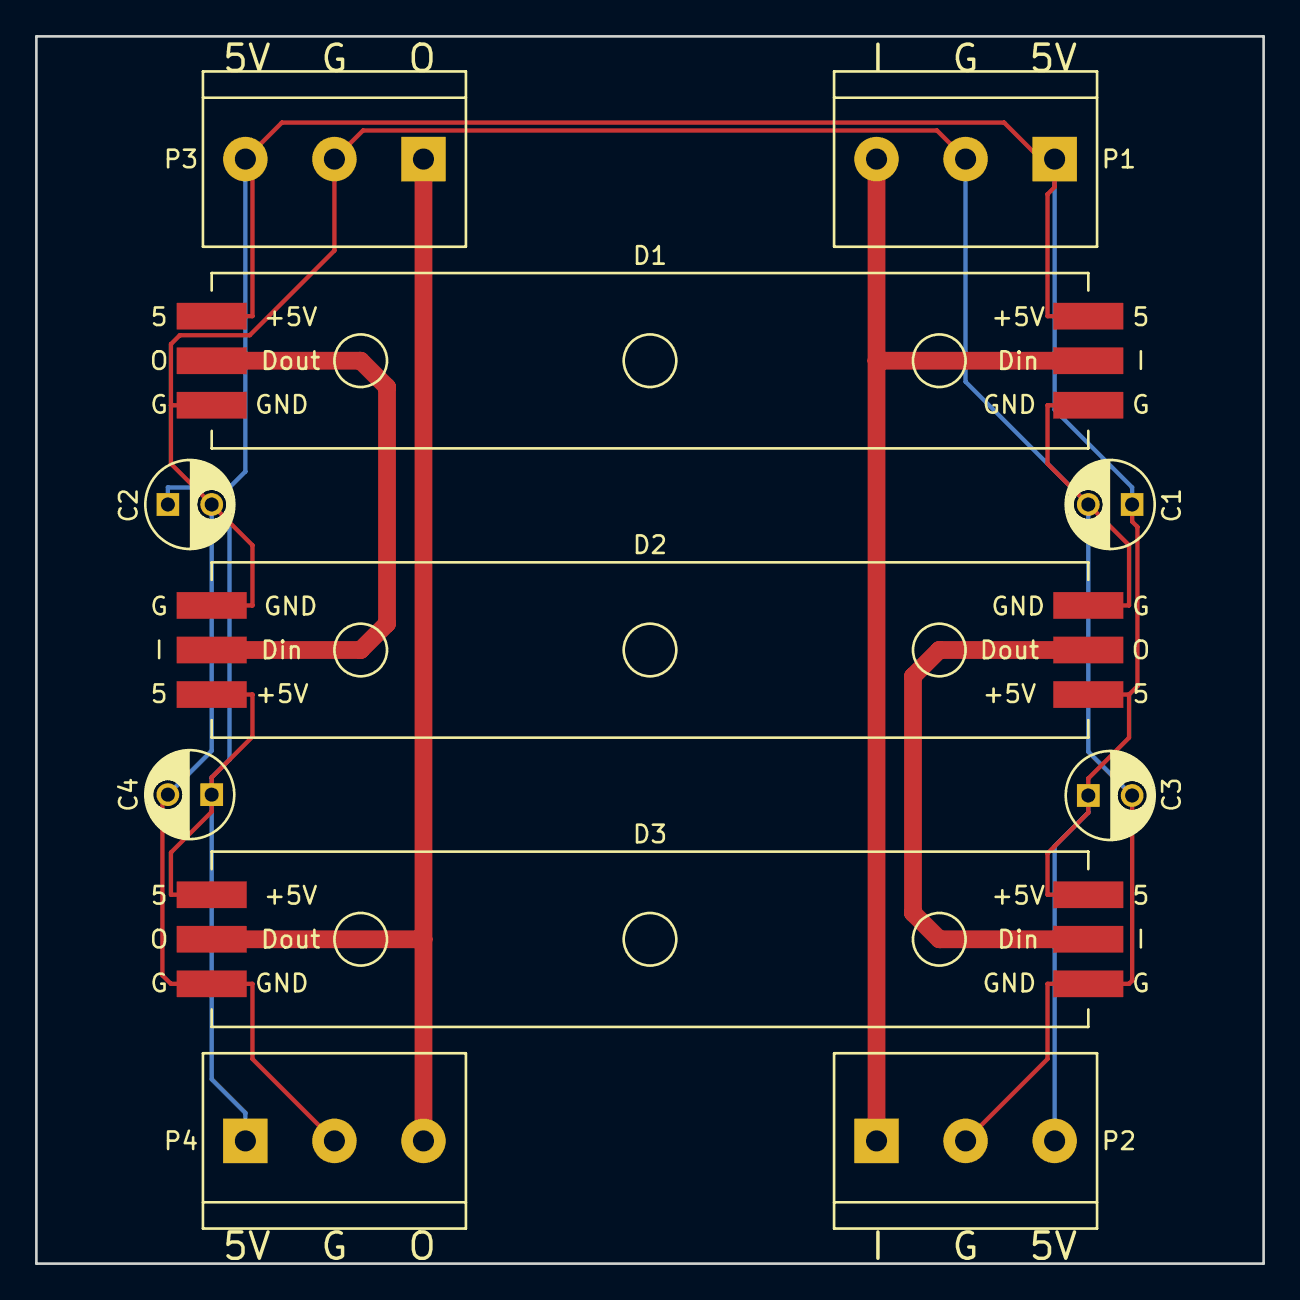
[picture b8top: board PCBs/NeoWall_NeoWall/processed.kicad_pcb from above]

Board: 2 copper layers, 70.0 x 70.0 mm, 11 parts (0 on the bottom side), 6 nets.

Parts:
C1, C2, C3, C4: 10u; C_Radial_D5_L6_P2.5
D1, D2, D3: Neopixelx3
P1, P2, P3, P4: CONN_01X03; bornier3

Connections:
+5V: C1.1, C2.1, C3.1, C4.1, D1.3, D1.4, D2.3, D2.4, D3.3, D3.4, P1.1, P2.3, P3.3, P4.1
GND: C1.2, C2.2, C3.2, C4.2, D1.1, D1.6, D2.1, D2.6, D3.1, D3.6, P1.2, P2.2, P3.2, P4.2
unnamed: D1.2, P1.3, P2.1
unnamed: D1.5, D2.2
unnamed: D2.5, D3.2
unnamed: D3.5, P3.1, P4.3

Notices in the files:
PCBs/MySensorsNode_LE-BOX-0028/processed.kicad_pcb:
Copyright (c) 2015 Patrick Fallberg
Licensed under CERN OHL v.1.2
